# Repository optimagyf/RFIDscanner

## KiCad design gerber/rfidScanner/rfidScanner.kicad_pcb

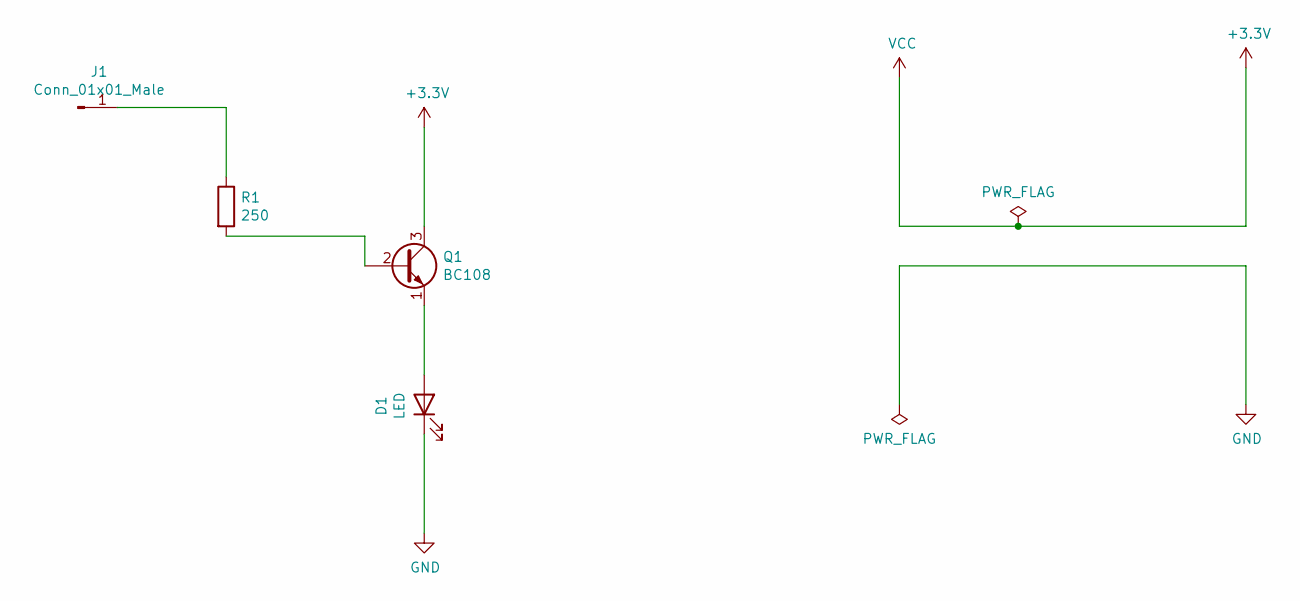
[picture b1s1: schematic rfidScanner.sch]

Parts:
D1: LED; LED_D5.0mm_Horizontal_O1.27mm_Z3.0mm
J1: Conn_01x01_Male; PinHeader_1x01_P2.54mm_Vertical
Q1: BC108; TO-18-3
R1: 250; R_Axial_DIN0207_L6.3mm_D2.5mm_P10.16mm_Horizontal

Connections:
+3V3: Q1.3 (C)
GND: D1.1 (K)
unnamed: D1.2 (A), Q1.1 (E)
unnamed: J1.1, R1.1
unnamed: Q1.2 (B), R1.2

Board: 2 copper layers, 4 parts (0 on the bottom side), 3 nets, no tracks yet.

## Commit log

2021-04-30 Retrieve previous working example.
2021-04-30 Use basic example configuration portal on switch of wifi manager library.
2021-05-03 Separate the wifi connexionduty to dedicated files
2021-05-03 Adjust pin number usage.
2021-05-03 Get a functional complete prototype again.
    Install the MFRC522 library to scan RFID tag. The module works
    well in SPI communication protocol. Possible to switch to I2C
    but not easy at all:
    https://forum.arduino.cc/t/rc522-rfid-rc522-switching-spi-to-uart-interface-or-i2c-possible/425741
    Retrieve the simple post server to test the communication.
2021-05-03 Scan and send an UID every second.
2021-05-12 Connect a screen in the prototype. Use a static IP address.
2021-05-12 Add referential document.
2021-05-13 Manage 2 interruption buttons and display message for each of them accordingly.
2021-05-13 Massive cleanup.
2021-05-13 Add concept example used for 3D print initiation.
2021-05-14 Separate the print concerne in display.{cpp,h} files
2021-06-12 Add begin of conception of electronic board.
2021-06-14 Avoid deprecated use of 'parseBody' in simplePostServer. Send UID as a string.
2021-06-14 Refactoring of the display module.
2021-06-15 Add a module to handle screen menu.
2021-06-15 Implementation of the menu structure.
2021-06-15 Display the ssid of the router connected to.
